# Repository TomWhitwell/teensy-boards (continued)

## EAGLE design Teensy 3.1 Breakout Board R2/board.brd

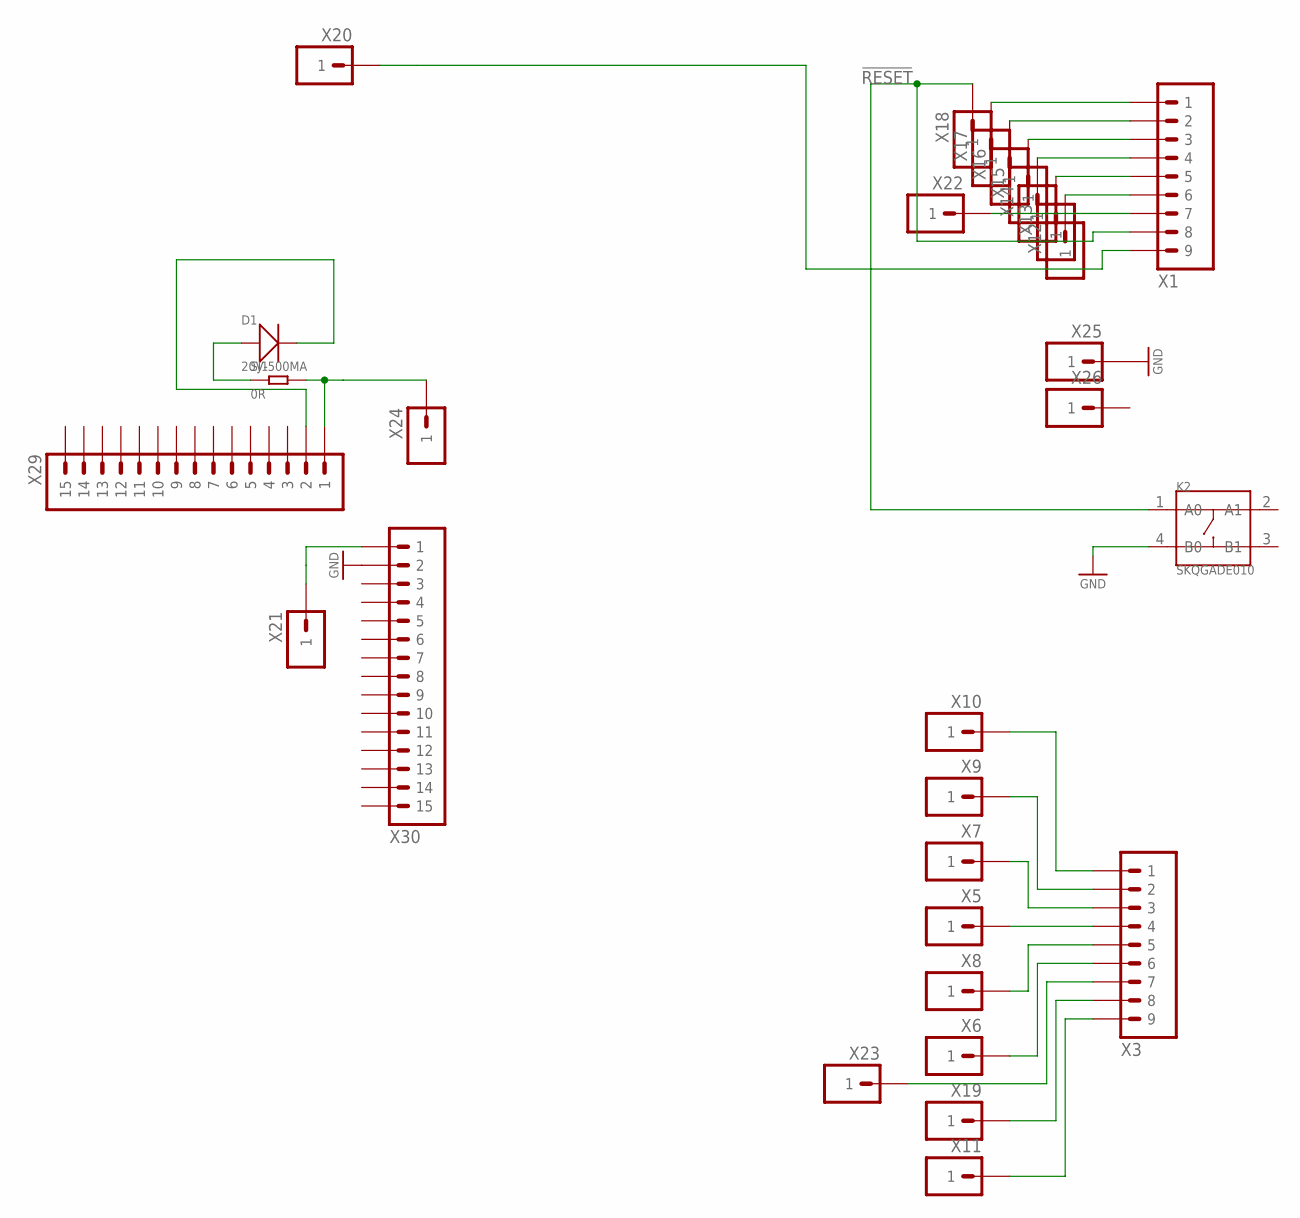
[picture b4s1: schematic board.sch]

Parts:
D1: 20V-500MA; SOD-123
K2: SKQGADE010; SW4-SMD-5.2X5.2X1.5MM
SJ1: 0R; R0805
X1, X3: 9P1/MIN_NOSILK; HEADER_1X9_1/MIN_NOSILK
X5, X6, X7, X8, X9, X10, X12, X13, X14, X15, X16, X17, X18, X25, X26: 1P; 1P_X
X11, X19, X20, X21, X22, X23, X24: 1P1/MIN_SILK2; HEADER_1X1_1/MIN_SILK2
X29, X30: 15P1/MIN_NOSILK; HEADER_1X15_1/MIN_NOSILK

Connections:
!RESET: K2.1 (A0), X1.8, X18.P$1
GND: K2.4 (B0), X25.P$1, X30.2
unnamed: X1.9, X20.1
unnamed: X3.9, X11.1
unnamed: X3.7, X23.1
unnamed: SJ1.2, X24.1, X29.1
unnamed: X1.1, X17.P$1
unnamed: X1.2, X16.P$1
unnamed: X1.3, X15.P$1
unnamed: X1.4, X14.P$1
unnamed: X1.5, X13.P$1
unnamed: X1.6, X12.P$1
unnamed: X21.1, X30.1
unnamed: X3.1, X10.P$1
unnamed: X3.2, X9.P$1
unnamed: X3.3, X7.P$1
unnamed: X3.4, X5.P$1
unnamed: X3.5, X8.P$1
unnamed: X3.6, X6.P$1
unnamed: D1.-, X29.2
unnamed: D1.+, SJ1.1
unnamed: X3.8, X19.1
unnamed: X1.7, X22.1

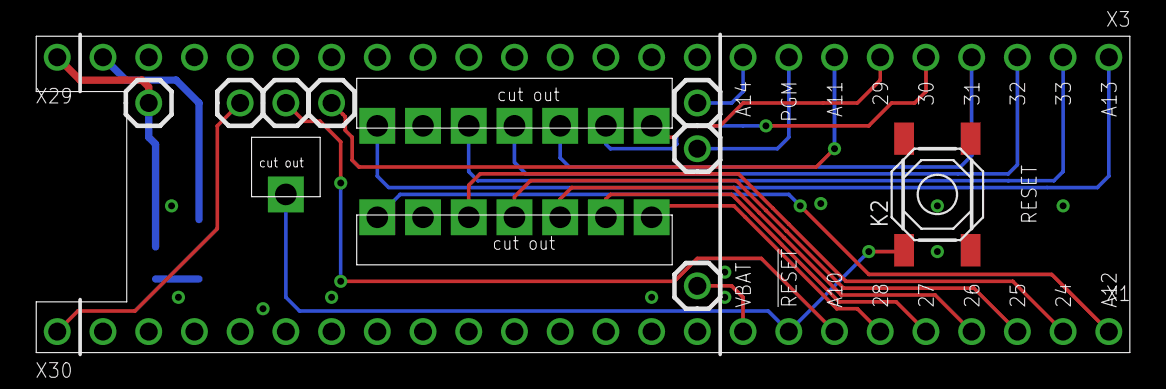
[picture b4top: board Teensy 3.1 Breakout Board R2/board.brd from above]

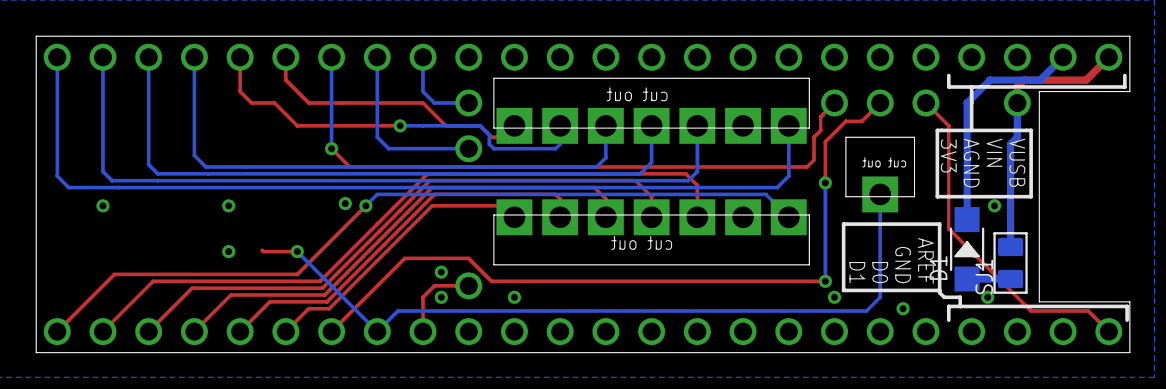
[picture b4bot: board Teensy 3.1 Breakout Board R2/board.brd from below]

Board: 2 copper layers, 60.8 x 17.6 mm, 29 parts (2 on the bottom side), 23 nets.

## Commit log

2015-11-14 new boards
2015-11-19 add 2.2" display adapter
2016-04-01 add T3.2 reference board clone
2016-04-01 change led and switch, add gerber files for osh park
2016-04-03 change usb mini from Hirose to Molex
2016-04-03 fix wrong mini usb part #
2016-04-07 fix wrong ferrite package
2016-04-10 add eagle dru and cam files for osh park 4 layer
2016-04-22 update bom
2016-04-29 update bom, add image
